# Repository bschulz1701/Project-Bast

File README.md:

# Project-Bast
Designs for a solar cell automated testing device

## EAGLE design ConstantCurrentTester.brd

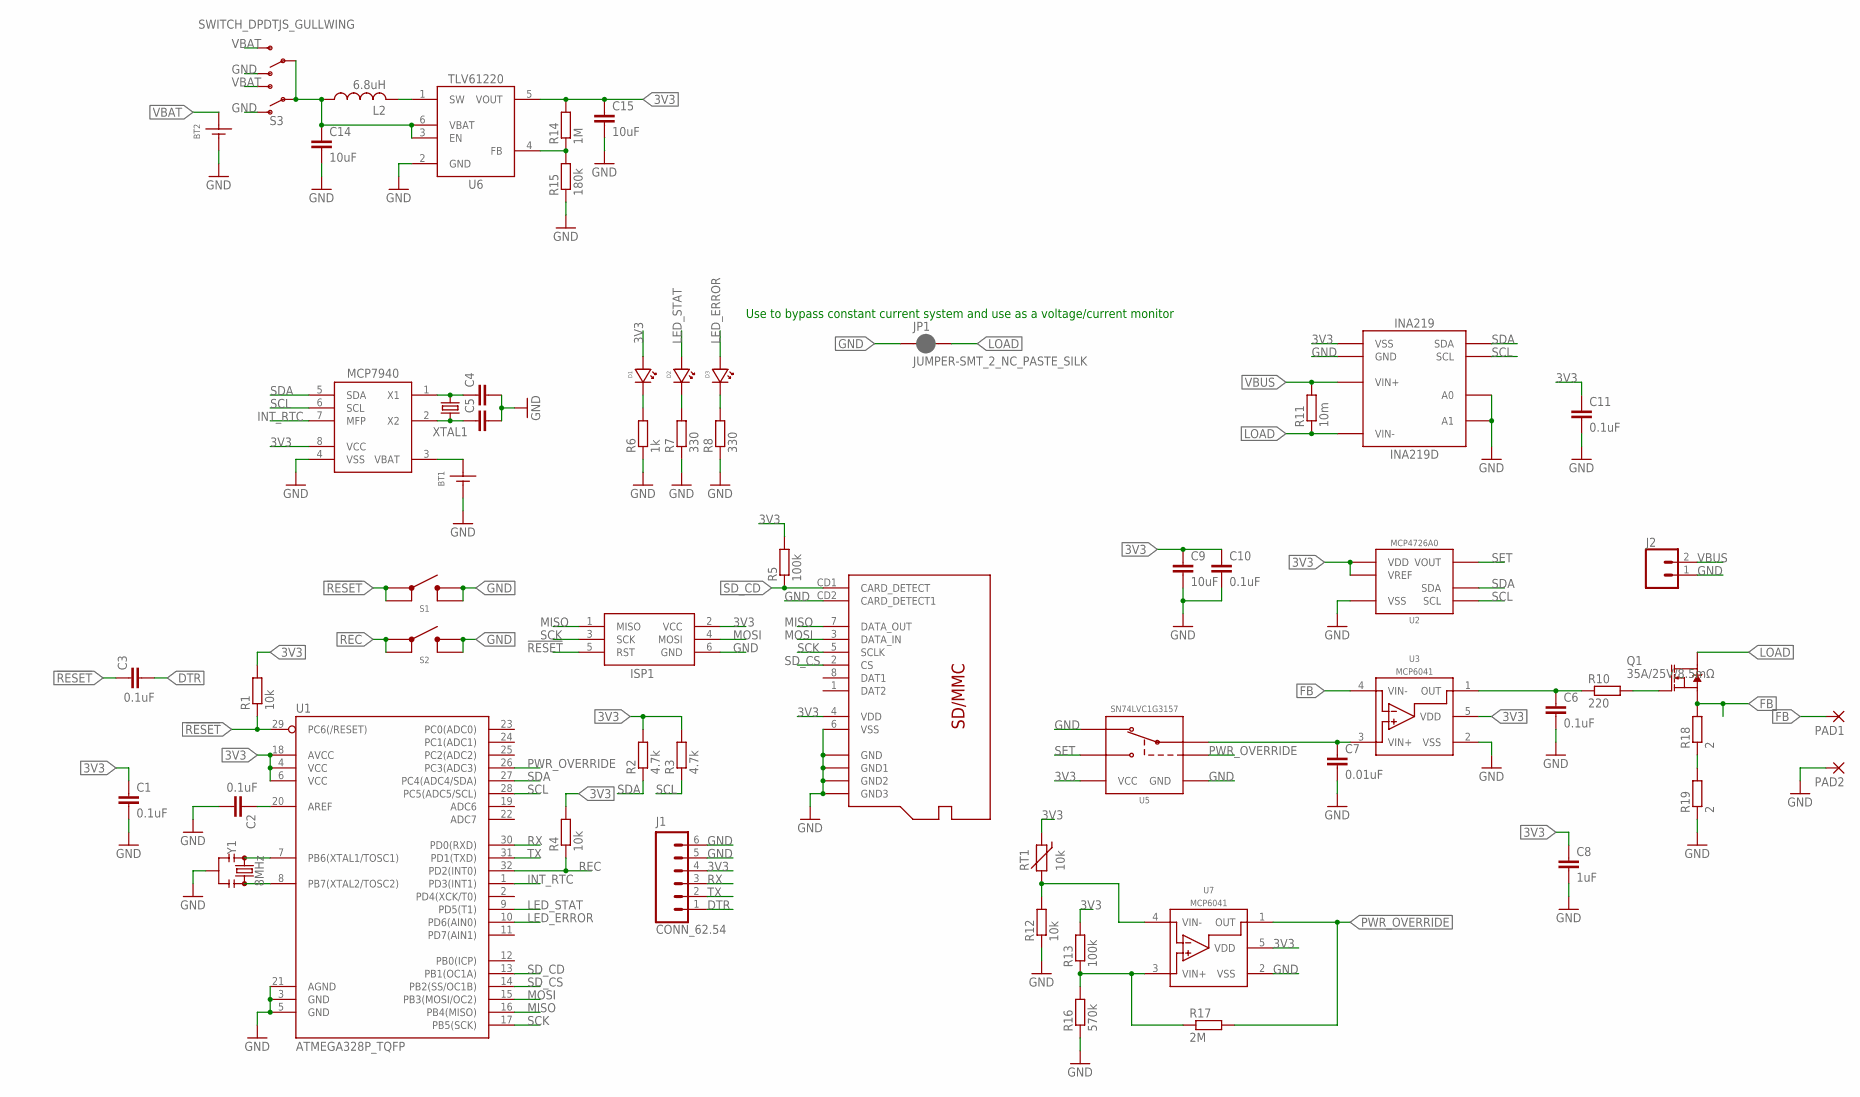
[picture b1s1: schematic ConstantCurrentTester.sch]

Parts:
BT1: BATTERY_COIN12MM; LINX_BAT-HLD-012-SMT
BT2: BATTERY_COINAA; BK-53
C1, C2, C3, C6, C10, C11: 0.1uF; C0603
C4, C5: C-EUC0603; C0603
C7: 0.01uF; C0603
C8: 1uF; C0603
C9, C14, C15: 10uF; C0805
D1: LEDBLUE0603; LED_0603
D2: LEDGREEN0603; LED_0603
D3: LEDRED0603; LED_0603
ISP1: AVRISP-6; AVRISP
J1: CONN_62.54; 1X06
J2: CONN_023.5MM; SCREWTERMINAL-3.5MM-2
JP1: JUMPER-SMT_2_NC_PASTE_SILK; SMT-JUMPER_2_NC_PASTE_SILK
L2: 6.8uH; 1008; MPN 74438323068; DIGIKEY 732-4849-1-ND
PAD1, PAD2: 3,81/1,4
Q1: 35A/25V/8.5mΩ; DPAK
R1, R4, R12: 10k; R0603
R2, R3: 4.7k; R0603
R5, R13: 100k; R0603
R6: 1k; R0603
R7, R8: 330; R0603
R10: 220; R0603
R11: 10m; R0805
R14: 1M; R0603
R15: 180k; R0603
R16: 570k; R0603
R17: 2M; R0603
R18, R19: 2; R2512
RT1: 10k; R0603; MPN ERT-J1VG103FA; DIGIKEY P12011CT-ND
S1, S2: BUTTON6X6_TH; SWITCH_6MM_TH
S3: SWITCH_DPDTJS_GULLWING; JS202011SCQN
U1: ATMEGA328P_TQFP; TQFP32-08
U2: MCP4726A0SOT-23; SOT23-6L
U3, U7: MCP6041; SOT23-5
U4: INA219D; SOIC_8
U5: SN74LVC1G3157SC70; DCK_R-PDSO-G6
U6: TLV61220DBV; DBV_R-PDSO-G6
U$1: MICRO_SD; CUSTOM-PARTS_SD_MICRO
U$2: MCP7940SOIC; SO08
XTAL1: CRYSTAL3.2X1.5; CRYSTAL_3.2X1.5_2-SMD
Y1: 8MHz; RESONATOR-SMD-3.2X1.3

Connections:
3V3: C1.1, C8.1, C9.1, C10.1, C11.1, C15.1, D1.ANODE, ISP1.2 (VCC), J1.4, R1.2, R2.2, R3.2, R4.2, R5.2, R13.2, R14.2, RT1.1 (2), U1.4 (VCC), U1.6 (VCC), U1.18 (AVCC), U2.3 (VDD), U2.6 (VREF), U3.5 (VDD), U4.5 (VSS), U5.5 (VCC), U6.5 (VOUT), U7.5 (VDD), U$1.4 (VDD), U$2.8 (VCC)
!RESET: C3.1, ISP1.5 (RST), R1.1, S1.1, S1.2, U1.29 (PC6(/RESET))
DRIVE: Q1.1 (G), R10.2
DTR: C3.2, J1.1
FB: PAD1.1, Q1.3 (S), R18.2, U3.4 (VIN-)
FB2: R14.1, R15.2, U6.4 (FB)
GND: BT1.GND (-), BT2.NEG@1 (-), BT2.NEG@2 (-), C1.2, C2.2, C4.2, C5.2, C6.2, C7.2, C8.2, C9.2, C10.2, C11.2, C14.2, C15.2, ISP1.6 (GND), J1.5, J1.6, J2.1, JP1.1, PAD2.1, R6.1, R7.1, R8.1, R12.1, R15.1, R16.1, R19.1, S1.3, S1.4, S2.3, S2.4, S3.1 (O1), S3.6 (O2), U1.3 (GND), U1.5 (GND), U1.21 (AGND), U2.2 (VSS), U3.2 (VSS), U4.1 (A1), U4.2 (A0), U4.6 (GND), U5.2 (GND), U5.3 (B1), U6.2 (GND), U7.2 (VSS), U$1.6 (VSS), U$1.CD2 (CARD_DETECT1), U$1.GND@1 (GND), U$1.GND@2 (GND1), U$1.GND@3 (GND2), U$1.GND@5 (GND3), U$2.4 (VSS), Y1.2
INT_RTC: U1.1 (PD3(INT1)), U$2.7 (MFP)
LED_ERROR: D3.ANODE, U1.10 (PD6(AIN0))
LED_STAT: D2.ANODE, U1.9 (PD5(T1))
LOAD: JP1.2, Q1.4 (D), R11.1, U4.7 (VIN-)
MISO: ISP1.1 (MISO), U1.16 (PB4(MISO)), U$1.7 (DATA_OUT)
MOSI: ISP1.4 (MOSI), U1.15 (PB3(MOSI/OC2)), U$1.3 (DATA_IN)
unnamed: U1.7 (PB6(XTAL1/TOSC1)), Y1.1
unnamed: U1.8 (PB7(XTAL2/TOSC2)), Y1.3
unnamed: C2.1, U1.20 (AREF)
unnamed: C4.1, U$2.1 (X1), XTAL1.P$1 (1)
unnamed: C5.1, U$2.2 (X2), XTAL1.P$2 (2)
unnamed: D1.CATHODE, R6.2
unnamed: D2.CATHODE, R7.2
unnamed: D3.CATHODE, R8.2
unnamed: C6.1, R10.1, U3.1 (OUT)
unnamed: R12.2, RT1.2 (1), U7.4 (VIN-)
unnamed: R13.1, R16.2, R17.1, U7.3 (VIN+)
unnamed: R18.1, R19.2
PWR_OVERRIDE: R17.2, U1.26 (PC3(ADC3)), U5.6 (S), U7.1 (OUT)
REC: R4.1, S2.1, S2.2, U1.32 (PD2(INT0))
RX: J1.3, U1.30 (PD0(RXD))
SCK: ISP1.3 (SCK), U1.17 (PB5(SCK)), U$1.5 (SCLK)
SCL: R3.1, U1.28 (PC5(ADC5/SCL)), U2.5 (SCL), U4.4 (SCL), U$2.6 (SCL)
SDA: R2.1, U1.27 (PC4(ADC4/SDA)), U2.4 (SDA), U4.3 (SDA), U$2.5 (SDA)
SD_CD: R5.1, U1.13 (PB1(OC1A)), U$1.CD1 (CARD_DETECT)
SD_CS: U1.14 (PB2(SS/OC1B)), U$1.2 (CS)
SET: C7.1, U2.1 (VOUT), U3.3 (VIN+), U5.1 (B2), U5.4 (A)
SW1: L2.2, U6.1 (SW)
TX: J1.2, U1.31 (PD1(TXD))
VBAT: BT2.POS@1 (+), BT2.POS@2 (+), S3.3 (S1), S3.4 (S2)
VBUS: J2.2, R11.2, U4.8 (VIN+)
VIN: C14.1, L2.1, S3.2 (P1), S3.5 (P2), U6.3 (EN), U6.6 (VBAT)
V_BACKUP: BT1.POWER0 (+), BT1.POWER1 (+), U$2.3 (VBAT)

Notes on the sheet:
Use to bypass constant current system and use as a voltage/current monitor

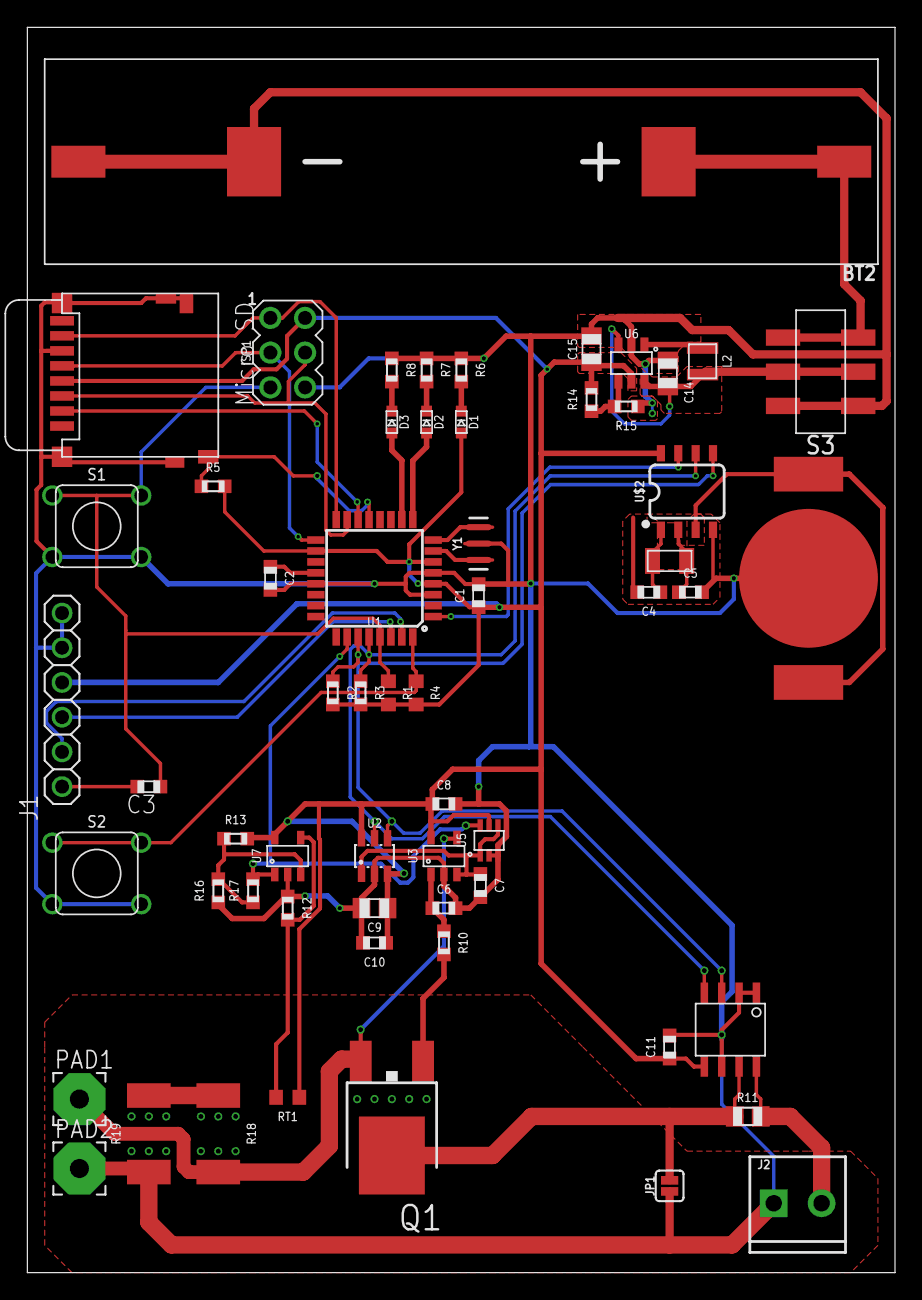
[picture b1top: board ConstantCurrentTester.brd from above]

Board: 2 copper layers, 63.5 x 91.1 mm, 59 parts (0 on the bottom side), 40 nets.

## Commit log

2020-01-24 Added licence
2020-01-24 Added beginnings of schematic for tester
2020-01-28 Preliminary schematic capture complete
2020-01-28 Initial board creation, no layout started
2020-01-28 Adapted Schematic, layout ready for review/cleanup
    Main layout complete, details and minor cleanup remain

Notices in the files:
parts and their libraries:
SparkFun-Jumpers: Licensing: Creative Commons ShareAlike 4.0 International - https://creativecommons.org/licenses/by-sa/4.0
